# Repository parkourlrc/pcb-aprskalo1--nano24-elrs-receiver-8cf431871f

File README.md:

# nano24 — 2.4 GHz ExpressLRS Receiver

A compact receiver hardware project from **Anthony Sprinkler**, built around an **ESP32-C3FH4** and **SX1281**. The PCB measures **13 × 11.1 mm** and connects to a flight controller through four bottom-edge CRSF cable pads.

**Status: untested hardware prototype.** CAD checks pass, but no assembled board has been powered, flashed or RF-tested. The custom printed Wi-Fi antenna and its matching network require measurement and tuning. No ready-to-flash firmware binary is included. Manufacturing files are provided for prototype review and quotation.

*CAD render of the proposed assembly; this is not a photograph of working hardware.*

[Open the schematic](exports/schematic/ELRS-Receiver.svg) · [View the PCB](ELRS-Receiver.kicad_pcb) · [BOM](exports/ELRS-Receiver-BOM.csv) · [Prototype Gerbers](exports/pcb/nano24-Gerbers-PROTOTYPE.zip) · [Test plan](TESTING.md)

## Hardware overview

| Feature | Current design |
| --- | --- |
| ELRS band | 2.4 GHz |
| Microcontroller | Espressif ESP32-C3FH4 |
| Radio | Semtech SX1281IMLTRT, single radio |
| Main ELRS antenna | External 2.4 GHz antenna through J1, U.FL connector |
| Wi-Fi antenna | Custom printed meander on B.Cu, integral PCB copper |
| Flight-controller interface | Full-duplex UART, CRSF, 3.3 V logic |
| Power input | Regulated 5 V through the `+` pad |
| Onboard regulator | TLV75533PDQNR, 3.3 V output |
| Clocks | 40 MHz MCU crystal; 52 MHz radio TCXO |
| Indication | RGB LED |
| Outline | 13 × 11.1 mm, chamfered corners |
| Proposed construction | Six copper layers, nominal 1.0 mm thickness |
| Assembly | 41 purchased parts: 22 front, 19 back |
| Wire connections | Four 1.8 × 1.6 mm lands with 0.6 mm castellated edge holes |
| Hardware revision | 0.4 in engineering metadata; board marking is simply `nano24` |

**The printed antenna serves Wi-Fi configuration and updates. The ELRS radio link uses a separate external antenna at J1.**

The circuit and parts of the dense core layout derive from [OpenDrone OpenRX Lite-UFL](https://github.com/OpenDrone-hw/OpenRX-Lite-UFL). This derivative changes the outline, antenna, cable pads and portions of the placement/routing. Full provenance is in [NOTICE.md](NOTICE.md). RadioMaster RP1 photographs informed packaging decisions; this is not a RadioMaster PCB reconstruction.

## Board views

| Front | Back |
| --- | --- |
|  |  |

The four cable-pad labels read **RX, TX, +, −** from left to right when viewed from the front with the U.FL connector toward the top. The printed Wi-Fi radiator is on the back along the edge opposite the main component cluster.

For closer inspection, see the [front copper plot](exports/pcb/PCB-top.svg), [back copper plot](exports/pcb/PCB-bottom.svg), [front assembly drawing](exports/pcb/PCB-assembly-top.svg) and [back assembly drawing](exports/pcb/PCB-assembly-bottom.svg). Bottom SVGs are mirrored for viewing from the physical back; manufacturing coordinates use one common board frame.

## Open and edit in KiCad

1. Install **KiCad 10** with its standard footprint and 3D-model libraries. The current files were checked with KiCad **10.0.7**.
2. Clone this repository or download and extract its ZIP.
3. Open [ELRS-Receiver.kicad_pro](ELRS-Receiver.kicad_pro) in KiCad.
4. Open [ELRS-Receiver.kicad_sch](ELRS-Receiver.kicad_sch) for the schematic or [ELRS-Receiver.kicad_pcb](ELRS-Receiver.kicad_pcb) for the PCB.
5. In PCB Editor, use **View → 3D Viewer** to inspect the assembly.

The native filenames retain the original `ELRS-Receiver` project basename. Project-local symbols, footprints and available custom models are included under [libraries/](libraries/), with relative library tables. Standard model references use KiCad's `KICAD10_3DMODEL_DIR`.

## Connect to a flight controller

| PCB marking | Reference | Connect to |
| --- | --- | --- |
| `RX` | TP1 | FC UART **TX** |
| `TX` | TP2 | FC UART **RX** |
| `+` | TP3 | Regulated **5 V** |
| `−` | TP4 | **GND** |
| `B` / round front pad | TP5 | BOOT / GPIO9; temporarily connect to GND for first flashing or recovery |

Use **3.3 V UART signal levels**. The `+` pad feeds the onboard regulator; it is not a direct battery input. The regulator's maximum operating input is 5.5 V. Provide strain relief for the soldered cable.

For Betaflight, enable **Serial RX** on the connected UART and select **Serial / CRSF** as the receiver mode/provider. Both signal wires are needed for communication in both directions, including FC-issued commands. See the [official ELRS FC setup guide](https://www.expresslrs.org/quick-start/receivers/configuring-fc/).

## Firmware and first flash

**The repository currently contains a hardware pin map, not a compiled firmware release or a registered nano24 Configurator target.**

The intended build family is **`Unified_ESP32C3_2400_RX`**, with [firmware/receiver-hardware.json](firmware/receiver-hardware.json) packaged into the firmware for this board. Selecting an arbitrary ESP32-C3 receiver target is not sufficient: its pin assignments and power configuration must match. RadioMaster RP1 ESP8285 firmware is incompatible with this MCU.

The first-flash workflow, once a complete board-specific UART image has been built, is:

1. Disconnect the receiver from the FC and fit the external ELRS antenna.
2. Connect a USB-to-UART adapter: adapter **TXD → RX**, **RXD → TX**, and **GND → −**. The adapter must use 3.3 V logic.
3. Supply regulated **5 V → +**, sharing ground with the adapter.
4. Connect **B → GND before applying power** to enter the ESP32-C3 ROM download mode.
5. Flash the complete board-specific image using its generated flash instructions, including the correct bootloader and partition data.
6. Remove the B-to-GND connection and power-cycle the receiver.

Later updates are intended to use UART, Betaflight passthrough or Wi-Fi. These paths remain untested on nano24. Wi-Fi operation also depends on the custom printed antenna performing adequately.

See [firmware/README.md](firmware/README.md) for the pin table, firmware work still needed and binding behavior. Reference: [ELRS ESP32-C3 build targets](https://github.com/ExpressLRS/ExpressLRS/blob/master/src/targets/esp32c3-rx.ini) and [Espressif download-mode guidance](https://docs.espressif.com/projects/esptool/en/latest/esp32c3/advanced-topics/boot-mode-selection.html).

## Binding

A physical bind button is not required. The intended options are:

- **Binding phrase:** configure the same phrase on the receiver and transmitter, using compatible firmware versions.
- **Betaflight:** support was introduced with ELRS 3.4.0, Betaflight 4.5.0 and Configurator 10.10. Use **Bind Receiver** or `bind_rx`, then **Bind** in the transmitter's ELRS Lua script.
- **Fresh unbound receiver:** ELRS can enter bind mode automatically when it has no saved binding or preset phrase. A previously bound receiver waiting for an absent transmitter is a different state.
- **Three quick power cycles:** the standard ELRS manual binding procedure, subject to firmware settings.

The `B` pad is GPIO9/BOOT. The current hardware JSON does **not** define a runtime button assignment, so a long-press binding action on B is not currently configured. Holding it low during startup enters the MCU bootloader instead.

The familiar delayed Wi-Fi startup is separate from binding. See the [official binding guide](https://www.expresslrs.org/quick-start/binding/) and [Web UI guide](https://www.expresslrs.org/quick-start/webui/). These are expected firmware capabilities, not completed nano24 hardware tests.

## Printed antenna and RF limits

AE1 replaces a purchased ceramic Wi-Fi antenna with a **custom meandered monopole prototype**. Its footprint is a single connected copper feature, excluded from the purchased BOM and pick/place data.

- Radiator: B.Cu, 0.18 mm trace width, 25.1 mm centreline length.
- Clearance strip: **2.05 × 5.7 mm** on all six copper layers, excluding plane fills and vias.
- Initial matching: **C21 = 1.2 pF, C22 = 1.2 pF, L2 = 2.5 nH**.
- Those values are provisional populations inherited from the reference circuit. They have **not** been matched to this printed radiator.

No antenna simulation, VNA tuning, radiated-efficiency measurement, sensitivity test or range test has been performed. Keep the antenna strip clear of nearby metal, batteries and wires in the eventual installation. Full dimensions, rationale and measurement requirements are in [ANTENNA-DESIGN.md](ANTENNA-DESIGN.md); the generated path is in [references/antenna-geometry.json](references/antenna-geometry.json).

## Fabrication and assembly files

| File or directory | Purpose |
| --- | --- |
| [Prototype Gerber ZIP](exports/pcb/nano24-Gerbers-PROTOTYPE.zip) | Six copper layers, masks, pastes, silkscreens, outline and drill files |
| [Manufacturing plots](exports/pcb/manufacturing/) | Individual fabrication files |
| [Schematic BOM](exports/ELRS-Receiver-BOM.csv) | Values, manufacturer parts, supplier fields and matching notes |
| [Assembler BOM](exports/pcb/JLCPCB-BOM.csv) | JLCPCB-format reference BOM |
| [Assembler CPL](exports/pcb/JLCPCB-CPL.csv) | Both-side component positions and native CAD rotations |
| [Native placement CSV](exports/pcb/ELRS-Receiver-positions.csv) | Original KiCad component placement output |

This board requires **double-sided precision assembly**, including 0201 components, and **filled/copper-capped via-in-pad processing**. The four 0.60 mm castellated edge holes must stay open; the smaller stitching/via-in-pad holes need the agreed filling treatment. Panel support, castellation manufacture, stack-up, RF impedance, fine silkscreen, rotations and sourcing require assembler/fabricator review.

The proposed stack is six layers at nominal 1.0 mm. It is not a confirmed fabricator stack code. BOM supplier fields are inherited selections, not verified current stock. The RF filter procurement replacement and RGB LED selection still need review. Read [FABRICATION-NOTES.md](FABRICATION-NOTES.md) before requesting a prototype quote.

## Verification and remaining tests

| Check | Recorded result |
| --- | --- |
| Schematic ERC | 0 violations |
| PCB DRC | 0 violations |
| Unconnected PCB items | 0 |
| Schematic/PCB parity findings | 0 |
| Physical net membership and firmware pin-map audit | Passed |
| Antenna strip / nearby ground-reference-layer geometry audit | Passed |
| Power-up and current consumption | Not tested |
| Firmware build and first flash | Not completed |
| CRSF, binding, telemetry and failsafe | Not tested |
| Antenna matching, sensitivity, Wi-Fi and range | Not tested |

Check reports are in [exports/ERC.json](exports/ERC.json), [exports/pcb/DRC.json](exports/pcb/DRC.json) and [exports/verification.json](exports/verification.json). They establish CAD connectivity and geometry, **not a functioning or flight-qualified receiver**.

The next work is documented in [TESTING.md](TESTING.md): source/DFM review, initial power-up, firmware packaging, clock verification, CRSF and binding tests, RF tuning, sensitivity and failsafe characterization. Record actual measurements and the tested hardware/firmware versions before changing a test to “passed.”

## Repository layout

```text
ELRS-Receiver.kicad_pro / .kicad_sch / .kicad_pcb
libraries/          Local symbols, footprints and custom 3D models
firmware/           Hardware pin mapping and flashing notes
references/         Generated antenna geometry
exports/            Schematic, BOM, PCB views and fabrication review files
tools/              CAD export and independent audit helpers
ANTENNA-DESIGN.md    Printed-antenna details and tuning requirements
FABRICATION-NOTES.md Stack, castellation and assembly requirements
TESTING.md          Hardware validation plan and results status
NOTICE.md           Source attribution and modification history
LICENSE             CERN-OHL-S-2.0 hardware license
```

Local KiCad session files, backups, temporary migration scripts, credentials and manufacturer datasheet PDF copies are excluded. See [tools/README.md](tools/README.md) for regenerating checks and exports, and [CONTRIBUTING.md](CONTRIBUTING.md) for contributing changes.

## Attribution and license

The hardware derives from **OpenDrone OpenRX Lite-UFL** and is distributed under **CERN-OHL-S-2.0**, preserving the upstream license and attribution. Source commits and modifications are recorded in [NOTICE.md](NOTICE.md). Standard KiCad library-derived assets retain the KiCad library licensing and exception described there.

ExpressLRS firmware is a separate upstream project with its own license; this repository does not include its firmware source or compiled binaries. nano24 is an independent Anthony Sprinkler project, with no claim of endorsement by ExpressLRS, OpenDrone or RadioMaster.

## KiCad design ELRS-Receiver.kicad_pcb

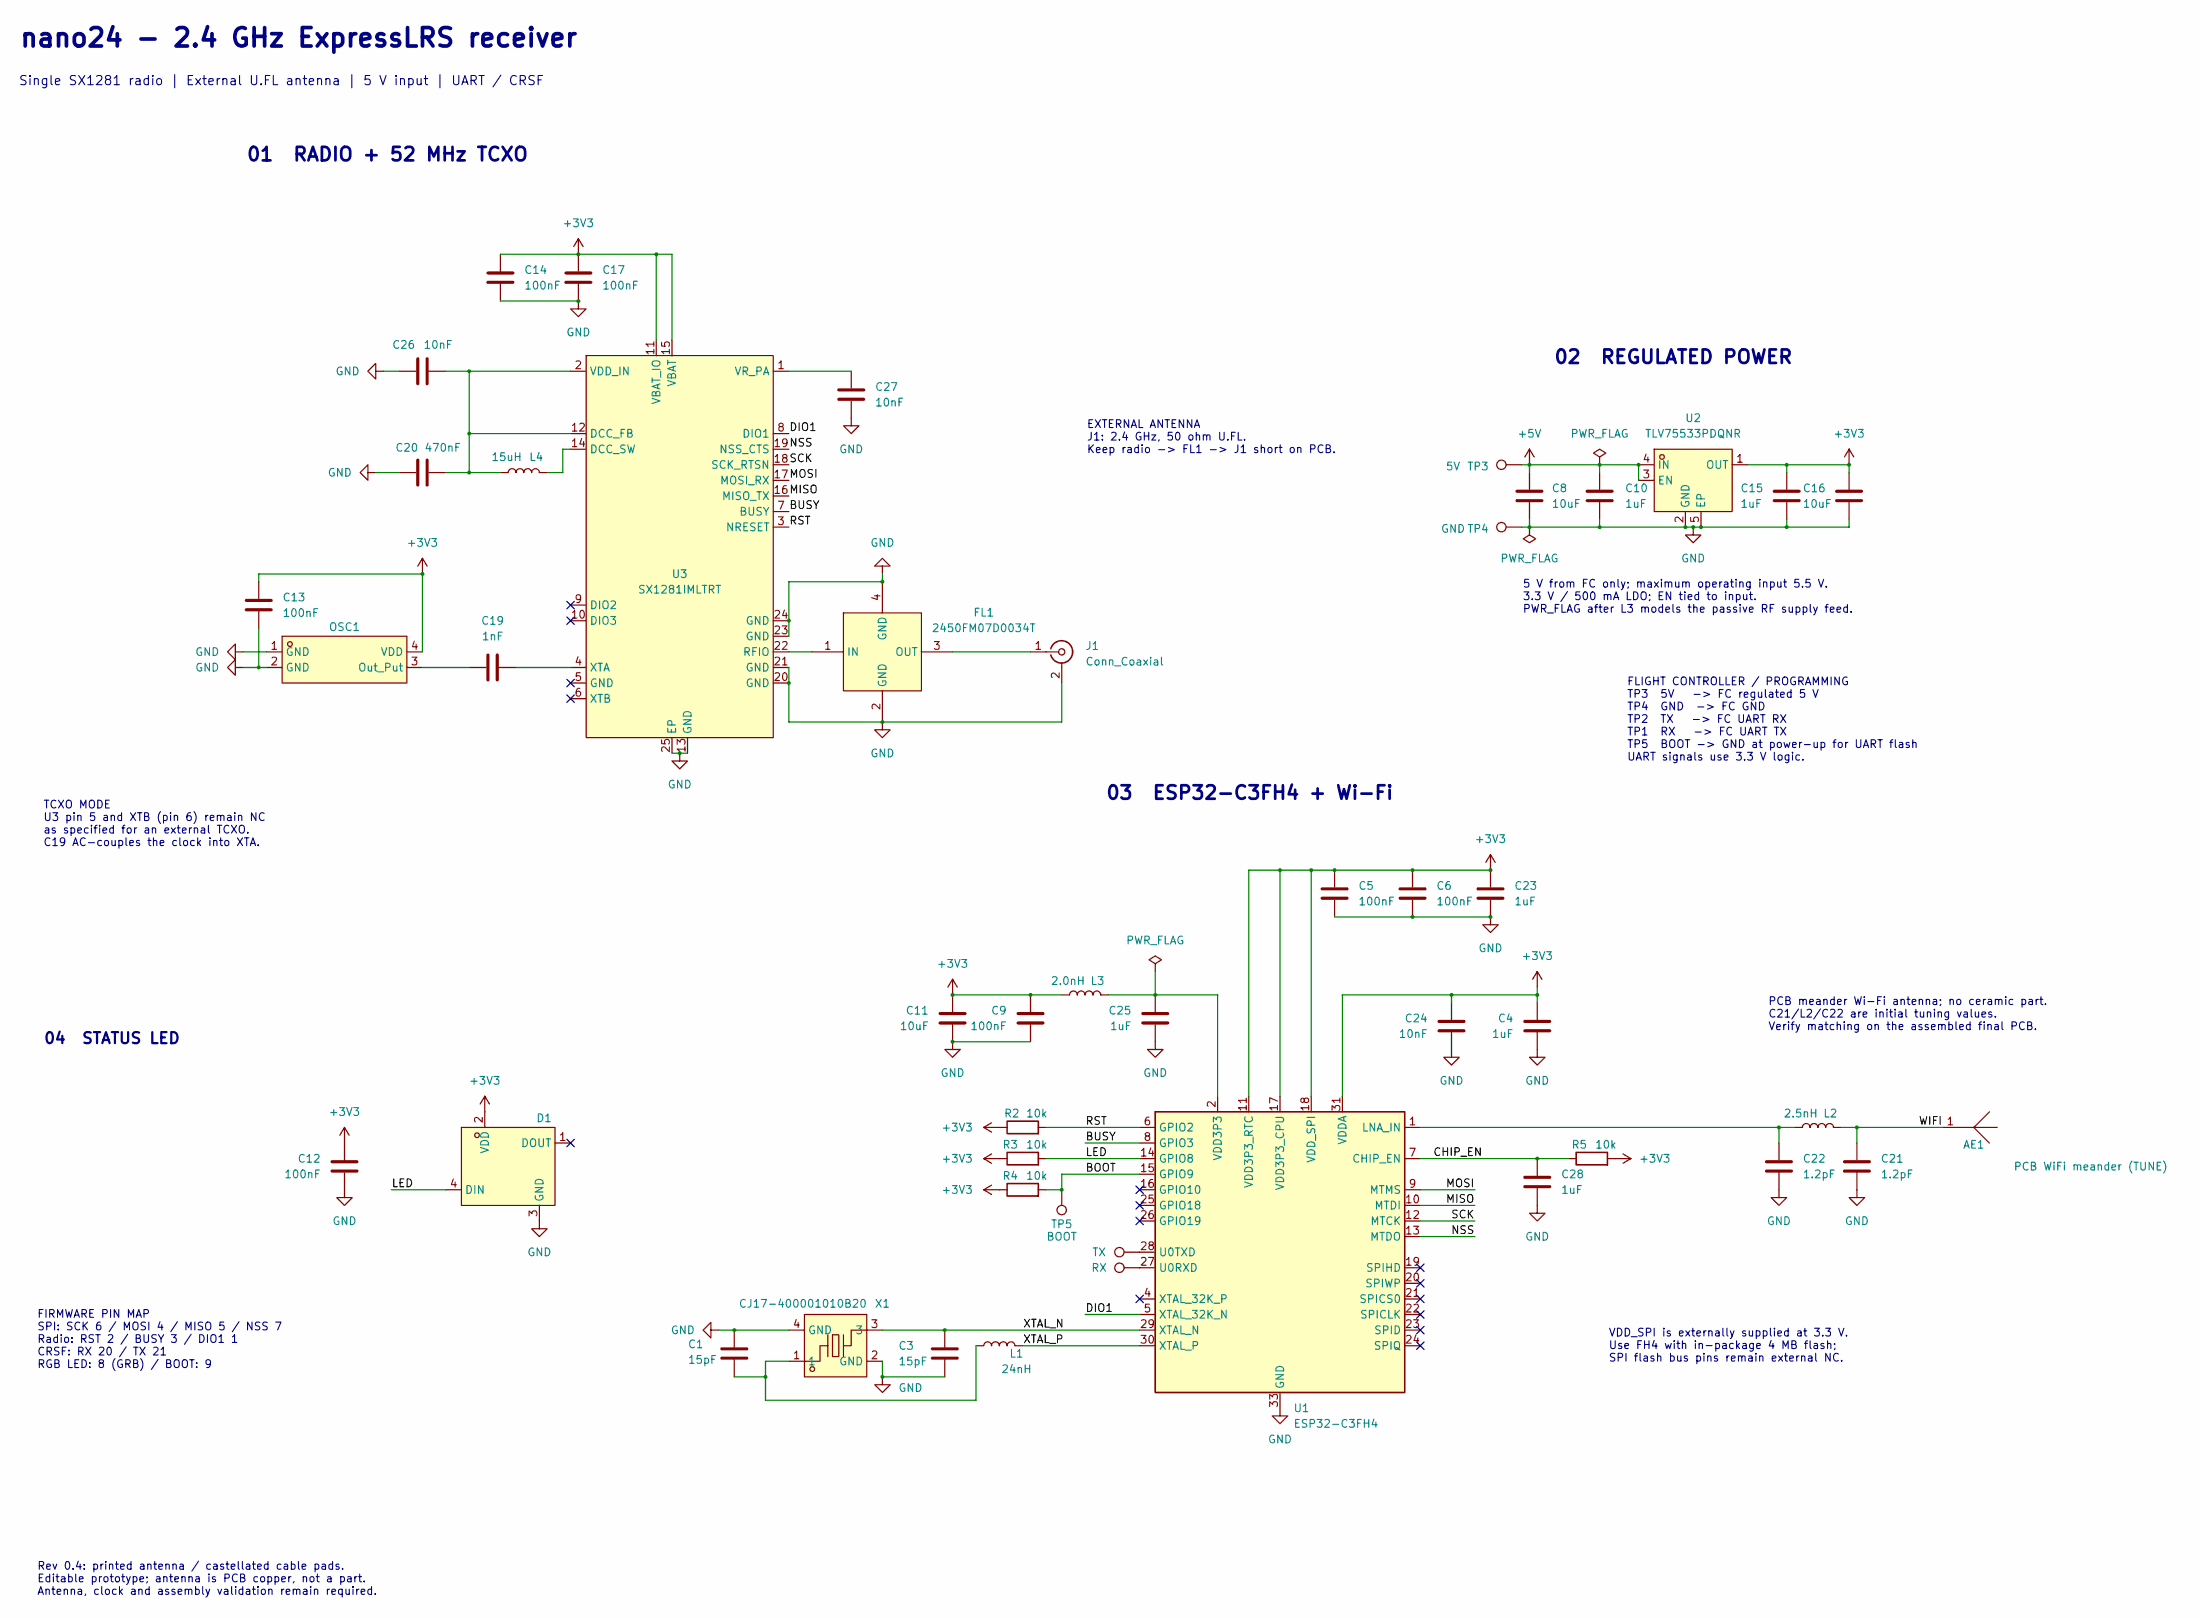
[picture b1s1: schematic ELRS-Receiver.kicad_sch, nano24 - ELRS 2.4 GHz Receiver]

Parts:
AE1: PCB WiFi meander (TUNE); PCB_Meander_2G4_v04; MPN PCB_FEATURE
C1: 15pF; C1_v04; MPN GRM0335C1H150JA01D; LCSC C85891
C3: 15pF; C3_v04; MPN GRM0335C1H150JA01D; LCSC C85891
C4: 1uF; C_0201_0603Metric_C4; MPN GRM033R61A105ME44D; LCSC C76935
C5: 100nF; C_0201_0603Metric_C5; MPN GRM033R61E104KE14D; LCSC C76939
C6: 100nF; C_0201_0603Metric_C6; MPN GRM033R61E104KE14D; LCSC C76939
C8: 10uF; C_0402_1005Metric_C8; MPN CL05A106MQ5NUNC; LCSC C15525
C9: 100nF; C_0201_0603Metric_C9; MPN GRM033R61E104KE14D; LCSC C76939
C10: 1uF; C_0201_0603Metric_C10; MPN GRM033R61A105ME44D; LCSC C76935
C11: 10uF; C_0402_1005Metric_C11; MPN GRM155R60J106ME44D; LCSC C76991
C12: 100nF; C_0201_0603Metric_C12; MPN GRM033R61E104KE14D; LCSC C76939
C13: 100nF; C_0201_0603Metric_C13; MPN GRM033R61E104KE14D; LCSC C76939
C14: 100nF; C_0201_0603Metric_C14; MPN GRM033R61E104KE14D; LCSC C76939
C15: 1uF; C_0201_0603Metric_C15; MPN GRM033R61A105ME44D; LCSC C76935
C16: 10uF; C_0402_1005Metric_C16; MPN CL05A106MQ5NUNC; LCSC C15525
C17: 100nF; C_0201_0603Metric_C17; MPN GRM033R61E104KE14D; LCSC C76939
C19: 1nF; C_0201_0603Metric_C19; MPN 0201B102K500NT; LCSC C66942
C20: 470nF; C_0201_0603Metric_C20; MPN GRM033R60J474KE90D; LCSC C85926
C21: 1.2pF; C21_v04; MPN GRM0335C1H1R2BA01D; LCSC C85895
C22: 1.2pF; C22_v04; MPN GRM0335C1H1R2BA01D; LCSC C85895
C23: 1uF; C_0201_0603Metric_C23; MPN GRM033R61A105ME44D; LCSC C76935
C24: 10nF; C_0201_0603Metric_C24; MPN GRM033R61A103KA01J; LCSC C2168164
C25: 1uF; C_0201_0603Metric_C25; MPN GRM033R61A105ME44D; LCSC C76935
C26: 10nF; C_0201_0603Metric_C26; MPN GRM033R61A103KA01J; LCSC C2168164
C27: 10nF; C_0201_0603Metric_C27; MPN GRM033R61A103KA01J; LCSC C2168164
C28: 1uF; C28_v04; MPN GRM033R61A105ME44D; LCSC C76935
D1: XL-1010RGBC-WS2812B; LED-SMD_4P-L1.0-W1.0-TL_XL-1010RGBC-WS2812B_D1; MPN XL-1010RGBC-2812B; LCSC C5349953
FL1: 2450FM07D0034T; FILTER-SMD_4P-L1.0-W0.5-L_FL1; MPN 2450FM07D0034T; LCSC Part_1 C2651081
J1: Conn_Coaxial; U.FL_Hirose_U.FL-R-SMT-1_Vertical_J1; MPN U.FL-R-SMT-1(80); LCSC C88374
L1: 24nH; L1_v04; MPN LQP03TN24NH02D; LCSC C206441
L2: 2.5nH; L2_v04; MPN LQP03TN2N5C02D; LCSC C206435
L3: 2.0nH; L_0201_0603Metric_L3; MPN LQP03TN2N0B02D; LCSC C86125
L4: 15uH; L_0805_2012Metric_L4; MPN MLZ2012M150WT000; LCSC C383402
OSC1: OW7EL89CENUNFAYLC-52M; OSC-SMD_4P-L2.0-W1.6-BL_TXC_7Z_OSC1; MPN OW7EL89CENUNFAYLC-52M; LCSC Part C22434896
R2: 10k; R_0201_0603Metric_R2; MPN RC0201FR-0710KL; LCSC C106225
R3: 10k; R_0201_0603Metric_R3; MPN RC0201FR-0710KL; LCSC C106225
R4: 10k; R_0201_0603Metric_R4; MPN RC0201FR-0710KL; LCSC C106225
R5: 10k; R5_v04; MPN RC0201FR-0710KL; LCSC C106225
TP1: RX; Castellated_WirePad_v04
TP2: TX; Castellated_WirePad_v04
TP3: 5V; Castellated_WirePad_v04
TP4: GND; Castellated_WirePad_v04
TP5: BOOT; BootPad_Front_v04
U1: ESP32-C3FH4; ESP32C3_QFN32_EP3.7_U1; MPN ESP32-C3FH4; LCSC C2858491
U2: TLV75533PDQNR; X2SON-4_L1.0-W1.0-P0.65-TL-EP_U2; MPN TLV75533PDQNR; LCSC Part C2861882
U3: SX1281IMLTRT; QFN-24_L4.0-W4.0-P0.50-TL-EP2.6_U3; MPN SX1281IMLTRT; LCSC Part C2151551
X1: CJ17-400001010B20; X1_v04; MPN CJ17-400001010B20; LCSC Part C2875272

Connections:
+3V3: C4.1, C5.1, C6.1, C9.1, C11.1, C12.1, C13.1, C14.1, C15.1, C16.1, C17.1, C23.1, C24.1, D1.2 (VDD), L3.2, OSC1.4 (VDD), R2.1, R3.1, R4.1, R5.2, U1.11 (VDD3P3_RTC), U1.17 (VDD3P3_CPU), U1.18 (VDD_SPI), U1.31 (VDDA), U1.32 (VDDA), U2.1 (OUT), U3.11 (VBAT_IO), U3.15 (VBAT)
+5V: C8.1, C10.1, TP3.1, U2.3 (EN), U2.4 (IN)
/BOOT: R4.2, TP5.1, U1.15 (GPIO9)
/BUSY: U1.8 (GPIO3), U3.7 (BUSY)
/CHIP_EN: C28.1, R5.1, U1.7 (CHIP_EN)
/DIO1: U1.5 (XTAL_32K_N), U3.8 (DIO1)
/LED: D1.4 (DIN), R3.2, U1.14 (GPIO8)
/MISO: U1.10 (MTDI), U3.16 (MISO_TX)
/MOSI: U1.9 (MTMS), U3.17 (MOSI_RX)
/NSS: U1.13 (MTDO), U3.19 (NSS_CTS)
/RST: R2.2, U1.6 (GPIO2), U3.3 (NRESET)
/SCK: U1.12 (MTCK), U3.18 (SCK_RTSN)
/WIFI: AE1.1, C21.1, L2.1
/XTAL_N: C3.1, U1.29 (XTAL_N), X1.3
/XTAL_P: L1.2, U1.30 (XTAL_P)
GND: C1.2, C3.2, C4.2, C5.2, C6.2, C8.2, C9.2, C10.2, C11.2, C12.2, C13.2, C14.2, C15.2, C16.2, C17.2, C20.1, C21.2, C22.2, C23.2, C24.2, C25.2, C26.1, C27.2, C28.2, D1.3 (GND), FL1.2 (GND), FL1.4 (GND), J1.2 (Ext), OSC1.1 (GND), OSC1.2 (GND), TP4.1, U1.33 (GND), U2.2 (GND), U2.5 (EP), U3.13 (GND), U3.20 (GND), U3.21 (GND), U3.23 (GND), U3.24 (GND), U3.25 (EP), X1.2 (GND), X1.4 (GND)
unnamed: C1.1, L1.1, X1.1
unnamed: C25.1, L3.1, U1.2 (VDD3P3), U1.3 (VDD3P3)
unnamed: FL1.1 (IN), U3.22 (RFIO)
unnamed: FL1.3 (OUT), J1.1 (In)
unnamed: C19.1, OSC1.3 (Out_Put)
unnamed: C22.1, L2.2, U1.1 (LNA_IN)
unnamed: TP1.1, U1.27 (U0RXD)
unnamed: TP2.1, U1.28 (U0TXD)
unnamed: C20.2, C26.2, L4.1, U3.2 (VDD_IN), U3.12 (DCC_FB)
unnamed: L4.2, U3.14 (DCC_SW)
unnamed: C27.1, U3.1 (VR_PA)
unnamed: C19.2, U3.4 (XTA)

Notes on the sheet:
nano24 - 2.4 GHz ExpressLRS receiver
Single SX1281 radio | External U.FL antenna | 5 V input | UART / CRSF
01 RADIO + 52 MHz TCXO
02 REGULATED POWER
5 V from FC only; maximum operating input 5.5 V. 3.3 V / 500 mA LDO; EN tied to input. PWR_FLAG after L3 models the passive RF supply feed.
03 ESP32-C3FH4 + Wi-Fi
04 STATUS LED
EXTERNAL ANTENNA J1: 2.4 GHz, 50 ohm U.FL. Keep radio -> FL1 -> J1 short on PCB.
TCXO MODE U3 pin 5 and XTB (pin 6) remain NC as specified for an external TCXO. C19 AC-couples the clock into XTA.
FLIGHT CONTROLLER / PROGRAMMING TP3 5V -> FC regulated 5 V TP4 GND -> FC GND TP2 TX -> FC UART RX TP1 RX -> FC UART TX TP5 BOOT -> GND at power-up for UART flash UART signals use 3.3 V logic.
PCB meander Wi-Fi antenna; no ceramic part. C21/L2/C22 are initial tuning values. Verify matching on the assembled final PCB.
VDD_SPI is externally supplied at 3.3 V. Use FH4 with in-package 4 MB flash; SPI flash bus pins remain external NC.
FIRMWARE PIN MAP SPI: SCK 6 / MOSI 4 / MISO 5 / NSS 7 Radio: RST 2 / BUSY 3 / DIO1 1 CRSF: RX 20 / TX 21 RGB LED: 8 (GRB) / BOOT: 9
Rev 0.4: printed antenna / castellated cable pads. Editable prototype; antenna is PCB copper, not a part. Antenna, clock and assembly validation remain required.

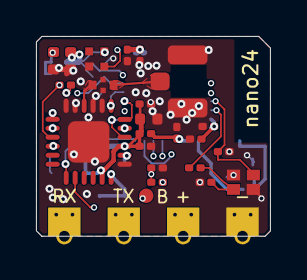
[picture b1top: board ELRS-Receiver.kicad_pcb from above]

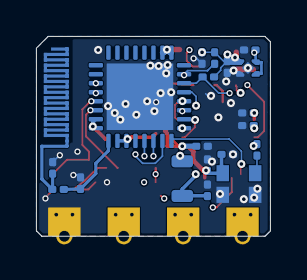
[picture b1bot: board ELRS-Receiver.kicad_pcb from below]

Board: 6 copper layers, 13.0 x 11.1 mm, 47 parts (20 on the bottom side), 28 nets.

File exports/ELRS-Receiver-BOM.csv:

"Designator","Value","MPN","Manufacturer","LCSC","Footprint","Quantity","TuningNote"
"C1","15pF","GRM0335C1H150JA01D","muRata","C85891","RX_V04:C1_v04","1",""
"C3","15pF","GRM0335C1H150JA01D","muRata","C85891","RX_V04:C3_v04","1",""
"C4","1uF","GRM033R61A105ME44D","muRata","C76935","RX_Compact:C_0201_0603Metric_C4","1",""
"C5","100nF","GRM033R61E104KE14D","muRata","C76939","RX_Compact:C_0201_0603Metric_C5","1",""
"C6","100nF","GRM033R61E104KE14D","muRata","C76939","RX_Compact:C_0201_0603Metric_C6","1",""
"C8","10uF","CL05A106MQ5NUNC","Samsung Electro-Mechanics","C15525","RX_Compact:C_0402_1005Metric_C8","1",""
"C9","100nF","GRM033R61E104KE14D","muRata","C76939","RX_Compact:C_0201_0603Metric_C9","1",""
"C10","1uF","GRM033R61A105ME44D","muRata","C76935","RX_Compact:C_0201_0603Metric_C10","1",""
"C11","10uF","GRM155R60J106ME44D","muRata","C76991","RX_Compact:C_0402_1005Metric_C11","1",""
"C12","100nF","GRM033R61E104KE14D","muRata","C76939","RX_Compact:C_0201_0603Metric_C12","1",""
"C13","100nF","GRM033R61E104KE14D","muRata","C76939","RX_Compact:C_0201_0603Metric_C13","1",""
"C14","100nF","GRM033R61E104KE14D","muRata","C76939","RX_Compact:C_0201_0603Metric_C14","1",""
"C15","1uF","GRM033R61A105ME44D","muRata","C76935","RX_Compact:C_0201_0603Metric_C15","1",""
"C16","10uF","CL05A106MQ5NUNC","Samsung Electro-Mechanics","C15525","RX_Compact:C_0402_1005Metric_C16","1",""
"C17","100nF","GRM033R61E104KE14D","muRata","C76939","RX_Compact:C_0201_0603Metric_C17","1",""
"C19","1nF","0201B102K500NT","FH","C66942","RX_Compact:C_0201_0603Metric_C19","1",""
"C20","470nF","GRM033R60J474KE90D","muRata","C85926","RX_Compact:C_0201_0603Metric_C20","1",""
"C21","1.2pF","GRM0335C1H1R2BA01D","muRata","C85895","RX_V04:C21_v04","1","Initial population only; retune for printed antenna on assembled board"
"C22","1.2pF","GRM0335C1H1R2BA01D","muRata","C85895","RX_V04:C22_v04","1","Initial population only; retune for printed antenna on assembled board"
"C23","1uF","GRM033R61A105ME44D","muRata","C76935","RX_Compact:C_0201_0603Metric_C23","1",""
"C24","10nF","GRM033R61A103KA01J","muRata","C2168164","RX_Compact:C_0201_0603Metric_C24","1",""
"C25","1uF","GRM033R61A105ME44D","muRata","C76935","RX_Compact:C_0201_0603Metric_C25","1",""
"C26","10nF","GRM033R61A103KA01J","muRata","C2168164","RX_Compact:C_0201_0603Metric_C26","1",""
"C27","10nF","GRM033R61A103KA01J","muRata","C2168164","RX_Compact:C_0201_0603Metric_C27","1",""
"C28","1uF","GRM033R61A105ME44D","muRata","C76935","RX_V04:C28_v04","1",""
"D1","XL-1010RGBC-WS2812B","XL-1010RGBC-2812B","XINGLIGHT","C5349953","RX_Compact:LED-SMD_4P-L1.0-W1.0-TL_XL-1010RGBC-WS2812B_D1","1",""
"FL1","2450FM07D0034T","2450FM07D0034T","JOHANSON(约翰逊)","C2651081","RX_Compact:FILTER-SMD_4P-L1.0-W0.5-L_FL1","1",""
"J1","Conn_Coaxial","U.FL-R-SMT-1(80)","HRS","C88374","RX_Compact:U.FL_Hirose_U.FL-R-SMT-1_Vertical_J1","1",""
"L1","24nH","LQP03TN24NH02D","muRata","C206441","RX_V04:L1_v04","1",""
"L2","2.5nH","LQP03TN2N5C02D","muRata","C206435","RX_V04:L2_v04","1","Initial population only; retune for printed antenna on assembled board"
"L3","2.0nH","LQP03TN2N0B02D","muRata","C86125","RX_Compact:L_0201_0603Metric_L3","1",""
"L4","15uH","MLZ2012M150WT000","Murata Electronics","C383402","RX_Compact:L_0805_2012Metric_L4","1",""
"OSC1","OW7EL89CENUNFAYLC-52M","OW7EL89CENUNFAYLC-52M","YXC Crystal Oscillators","C22434896","RX_Compact:OSC-SMD_4P-L2.0-W1.6-BL_TXC_7Z_OSC1","1",""
"R2","10k","RC0201FR-0710KL","YAGEO","C106225","RX_Compact:R_0201_0603Metric_R2","1",""
"R3","10k","RC0201FR-0710KL","YAGEO","C106225","RX_Compact:R_0201_0603Metric_R3","1",""
"R4","10k","RC0201FR-0710KL","YAGEO","C106225","RX_Compact:R_0201_0603Metric_R4","1",""
"R5","10k","RC0201FR-0710KL","YAGEO","C106225","RX_V04:R5_v04","1",""
"U1","ESP32-C3FH4","ESP32-C3FH4","Espressif Systems","C2858491","RX_Compact:ESP32C3_QFN32_EP3.7_U1","1",""
"U2","TLV75533PDQNR","TLV75533PDQNR","TI","C2861882","RX_Compact:X2SON-4_L1.0-W1.0-P0.65-TL-EP_U2","1",""
"U3","SX1281IMLTRT","SX1281IMLTRT","SEMTECH","C2151551","RX_Compact:QFN-24_L4.0-W4.0-P0.50-TL-EP2.6_U3","1",""
"X1","CJ17-400001010B20","CJ17-400001010B20","JSCJ","C2875272","RX_V04:X1_v04","1",""
